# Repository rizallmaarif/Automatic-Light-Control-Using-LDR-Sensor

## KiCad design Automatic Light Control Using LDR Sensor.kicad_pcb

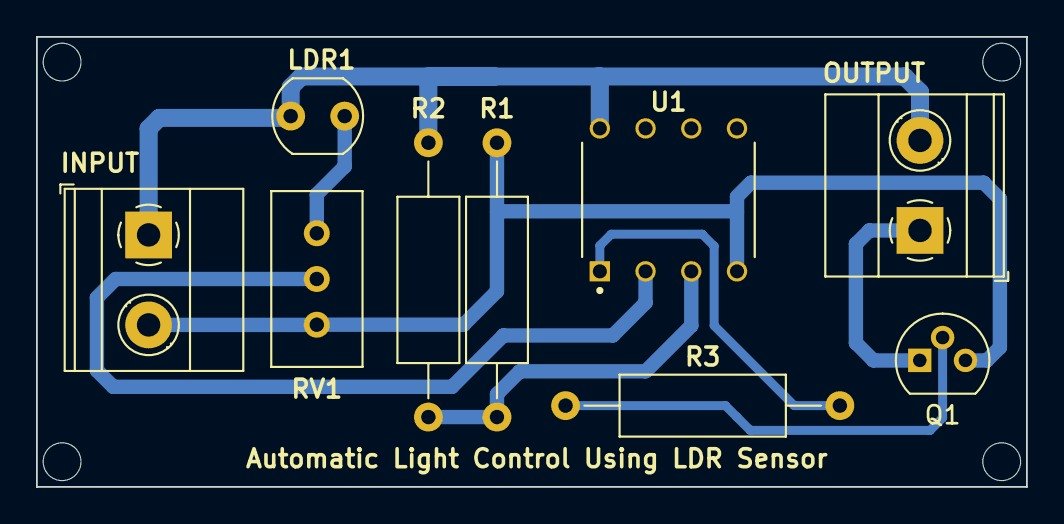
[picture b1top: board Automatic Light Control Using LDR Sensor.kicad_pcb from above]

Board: 2 copper layers, 55.0 x 25.0 mm, 9 parts (0 on the bottom side), 8 nets.

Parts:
INPUT: Screw_Terminal_01x02; TerminalBlock_Phoenix_MKDS-1,5-2_1x02_P5.00mm_Horizontal
LDR1: R_LDR_5.0x4.1mm_P3mm_Vertical
OUTPUT: Screw_Terminal_01x02; TerminalBlock_Phoenix_MKDS-1,5-2_1x02_P5.00mm_Horizontal
Q1: BC337; TO-92
R1, R2: 5.1K; R_Axial_DIN0309_L9.0mm_D3.2mm_P15.24mm_Horizontal
R3: 1K; R_Axial_DIN0309_L9.0mm_D3.2mm_P15.24mm_Horizontal
RV1: 10K; Potentiometer_Bourns_3296W_Vertical
U1: LM358PE3; DIP794W45P254L959H508Q8

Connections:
+12V: INPUT.1, LDR1.1, OUTPUT.1, R1.1, U1.8 (VCC(3V-32V))
GND: INPUT.2, Q1.3 (E), R2.2, RV1.3, U1.4 (GND)
unnamed: OUTPUT.2, Q1.1 (C)
unnamed: LDR1.2, RV1.1
unnamed: Q1.2 (B), R3.1
unnamed: R1.2, R2.1, U1.3 (1IN+)
unnamed: RV1.2, U1.2 (1IN-)
unnamed: R3.2, U1.1 (1OUT)
